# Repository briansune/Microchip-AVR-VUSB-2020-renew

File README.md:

# Microchip-AVR-VUSB-2020-renew

Firmware of the Atmega328 example is shown in the "atmega328_prj" with Microchip studio latest version supported on Windows OS platform.

The usb control on PC side is using python script rather than old C program as libusb-1.0 is tedious and hard to linkup and version support might not be easy.

The packed exe is enclosed on this example where the spec will give user a good example how to due with the error and dll linkage during pyinstaller.

This example only provide simple command line interface, while tkinter can be used to enhance the interface as well.

As always have fun =]

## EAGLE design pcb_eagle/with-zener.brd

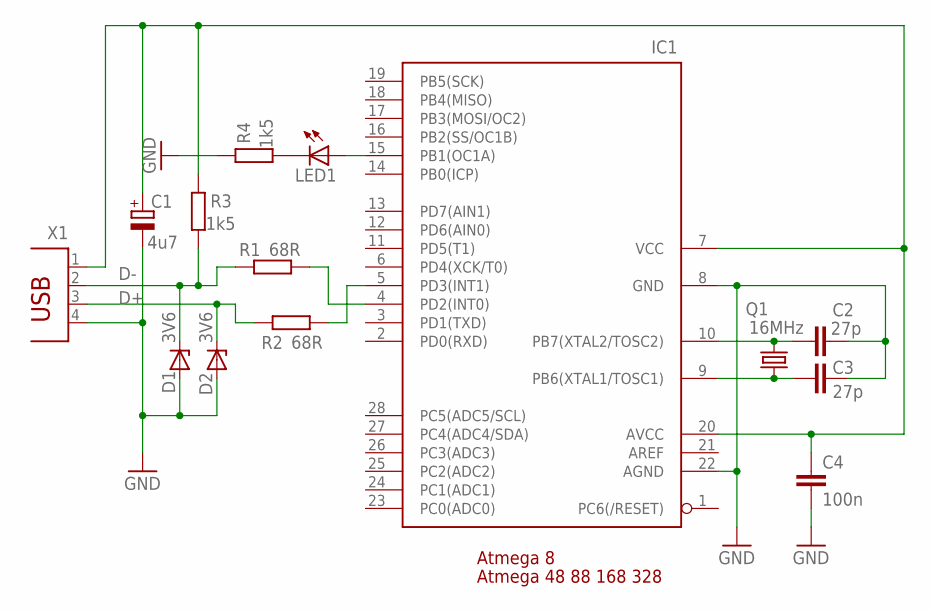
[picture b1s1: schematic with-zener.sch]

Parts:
C1: 4u7; E2-5
C2, C3: 27p; C025-024X044
C4: 100n; C025-024X044
D1, D2: 3V6; DO34Z7
IC1: ATMEGA8-16P; DIL28-3
LED1: LED-3MM
Q1: 16MHz; HC49U-V
R1, R2: 68R; 0207/10
R3, R4: 1k5; 0207/10
X1: PN61729

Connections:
D+: D2.C, R2.1, X1.3
D-: D1.C, R1.1, R3.1, X1.2
GND: C1.-, C2.2, C3.2, C4.2, D1.A, D2.A, IC1.8 (GND), IC1.22 (AGND), R4.2, X1.4
unnamed: IC1.4 (PD2(INT0)), R1.2
unnamed: IC1.5 (PD3(INT1)), R2.2
unnamed: IC1.15 (PB1(OC1A)), LED1.A
unnamed: LED1.K (C), R4.1
unnamed: C3.1, IC1.9 (PB6(XTAL1/TOSC1)), Q1.1
unnamed: C2.1, IC1.10 (PB7(XTAL2/TOSC2)), Q1.2
VCC: C1.+, C4.1, IC1.7 (VCC), IC1.20 (AVCC), R3.2, X1.1

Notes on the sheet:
Atmega 8
Atmega 48 88 168 328

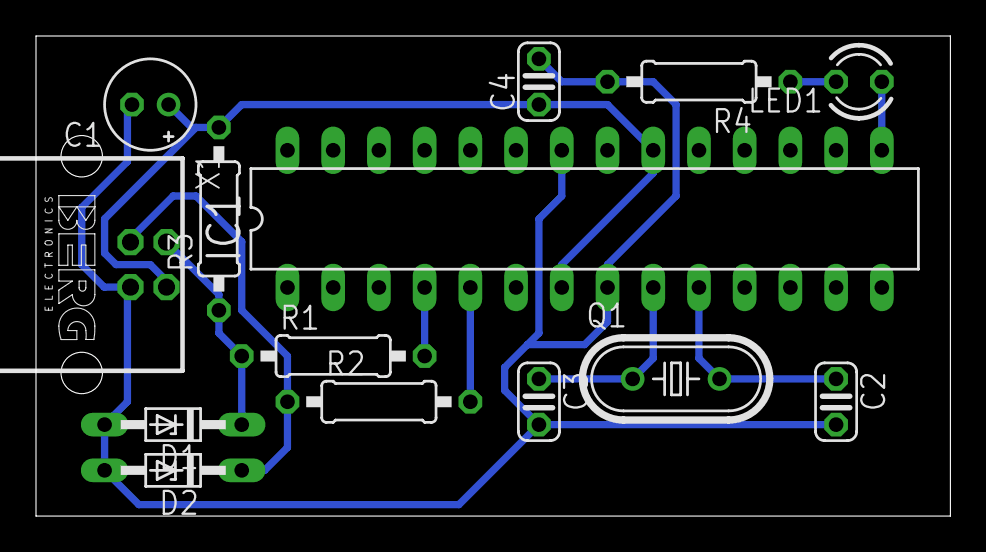
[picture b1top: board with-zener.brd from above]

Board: 2 copper layers, 50.8 x 26.7 mm, 14 parts (0 on the bottom side), 10 nets.

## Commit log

2020-12-17 Create LICENSE
2020-12-17 renew VUSB for AVR as new Microchip Atmel
2020-12-17 add cmd imgs
2020-12-17 add pcb eagle
